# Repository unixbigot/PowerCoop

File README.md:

# PowerCoop

A Power Coop is like a Power Bank but less suckful

## What is a power bank

A power bank is a battery of rechargeable electrical storage cells and some electronics to charge
and discharge.   Almost always USB connectors are used for charging and discharging.

Some have lights or small displays to report the State of Charge (SoC) and possibly the rate of charge/discharge.

They. All.  Suck.   

* Power banks lie egregiously about their capacity
* Power banks ruin cells through sloppy charge/discharge management
* Power banks do not cope with aging cells
* Power banks do not give accurate predictions of available runtime
* Power banks cannot be monitored to tell devices about their capacity and state
* Power banks are unfixable
* Power banks are typically closely coupled to one cell size and/or count

## What is a Power Coop

My vision for a power bank that does not suck

* Fast charging from USB power delivery, and raw DC
* Battery and cell health management (control over charge/discharge levels and rates, cell balancing)
* Multiple independent output channels, each with voltage and current measurement
* Programmable current limiting

Conceptually (per [JPM](https://aus.social/@jpm))  

```text
a battery bank with a bunch of high-power outputs
that all have power displays, also displaying
over Bluetooth, so you can run a phone, a laptop,
a soldering iron, a hotplate, and a couple of
devices under test from it.
```

@voltagex needs a power bank that can wirelessly report its state of charge, in approximately the same size as commercially-available 10,000mAh power banks.

@jpm wants a power bank that you don't need to screw around with, just plug in a USB-C cable and receive power. It needs to be a UPS for a RasPi.

## 6P process

### Problem - what do users want/need

See <https://github.com/unixbigot/PowerCoop/issues>

#### Must Have

* A battery
* USB-C output capable of providing 100W of USB-C PPS power
* USB-C charging at up to 100W
* Display
  * Per-port voltage and current
  * State of charge
  * Remote display via wireless link

#### Should Have

* Support different battery chemistries and number of cells
  * Li-I, LiFePo4, Lead-Acid
* Advanced battery controls
  * Charge limit (eg 80% limit) to prolong service life of Li-I cells
  * Cell balancing
* Advanced output port controls
  * Fixed 5V/3A output for USB-C devices that have broken USB-C CC implementations (eg Raspberry Pi 4)
  * Prevent port turning off on light load
* Modular
  * Battery board - battery charge controller, tells system board how much power is available
  * System board - main display, monitors available power and distributes among ports
  * Port board - receives allowable power level from system, per-port configuration and display
* Only USB-C ports, which reduces design complexity and BOM

#### Nice To Have

* Port board variants with configurable DC input/output or USB-A output
* Any-port charging - I just want to plug the charger in anywhere and it charges
* Able to use power tool battery packs
  * Effectively able to CHARGE power tool battery packs from USB-C!
* Power bank friend on the screen

### Proposal - how are we gonna solve the problem

We gonna make our own power bank that doesn't suck. Hopefully it won't be too much more expensive than power banks that do suck.

### Players - What partial solutions are out there

I (kit, @unixbigot) have or have ordered all of these:

* slightly less sucky power banks
  * <https://aliexpress.com/item/1005004645663172.html>
  * <https://aliexpress.com/item/1005007295821577.html>
  * <https://aliexpress.com/item/1005006988280869.html>
* Off the shelf battery management
  * <https://aliexpress.com/item/1005006071626722.html>
* Microcontroller with PD support
  * <https://aliexpress.com/item/1005005793197807.html>
  * <https://aliexpress.com/item/1005005793197807.html>
* Various DC<->PD modules
  * <https://aliexpress.com/item/1005006463687480.html>
  * <https://aliexpress.com/item/1005006113132068.html>
  * <https://aliexpress.com/item/1005006738365927.html>
  * <https://aliexpress.com/item/1005006572686976.html>

@jpm also has a bunch of similar things, including the CH32X035 dev board and power banks of various suckage.

### Proof of concept - Validate feasibility, select Parts

Splitting the PowerCoop into parts allows us to develop and test different pieces in parallel.  There are 4 main parts to the PowerCoop - the system control, the (main) display, the power ports, and the battery control.

#### System Control

Use the display control SOC? Or should we have a dedicated processor for system (power status and allocation) functions?

#### Main Display

Probably [nRF52840](https://www.nordicsemi.com/Products/nRF52840), maybe other Bluetooth-enabled SOC. TBD what the UI screen/buttons/knobs/etc should be, definitely something that @voltagex would have opinions on.

#### Power Ports

Likely [CH32X035](https://www.wch-ic.com/products/CH32X035.html) as the brains and [TPS55288](https://www.ti.com/product/TPS55288) for the power delivery. TBD if each port should have a separate screen and control.

#### Battery Control

Maybe [LTC4015](https://www.analog.com/en/products/ltc4015.html) as a single unified charge controller, other possibility is to use a cheap SOC (CH32V003?) that abstracts the battery interface so each battery board can have something new and spicy.

### Prototype - Iterate a lot

### Product - deliver on promises

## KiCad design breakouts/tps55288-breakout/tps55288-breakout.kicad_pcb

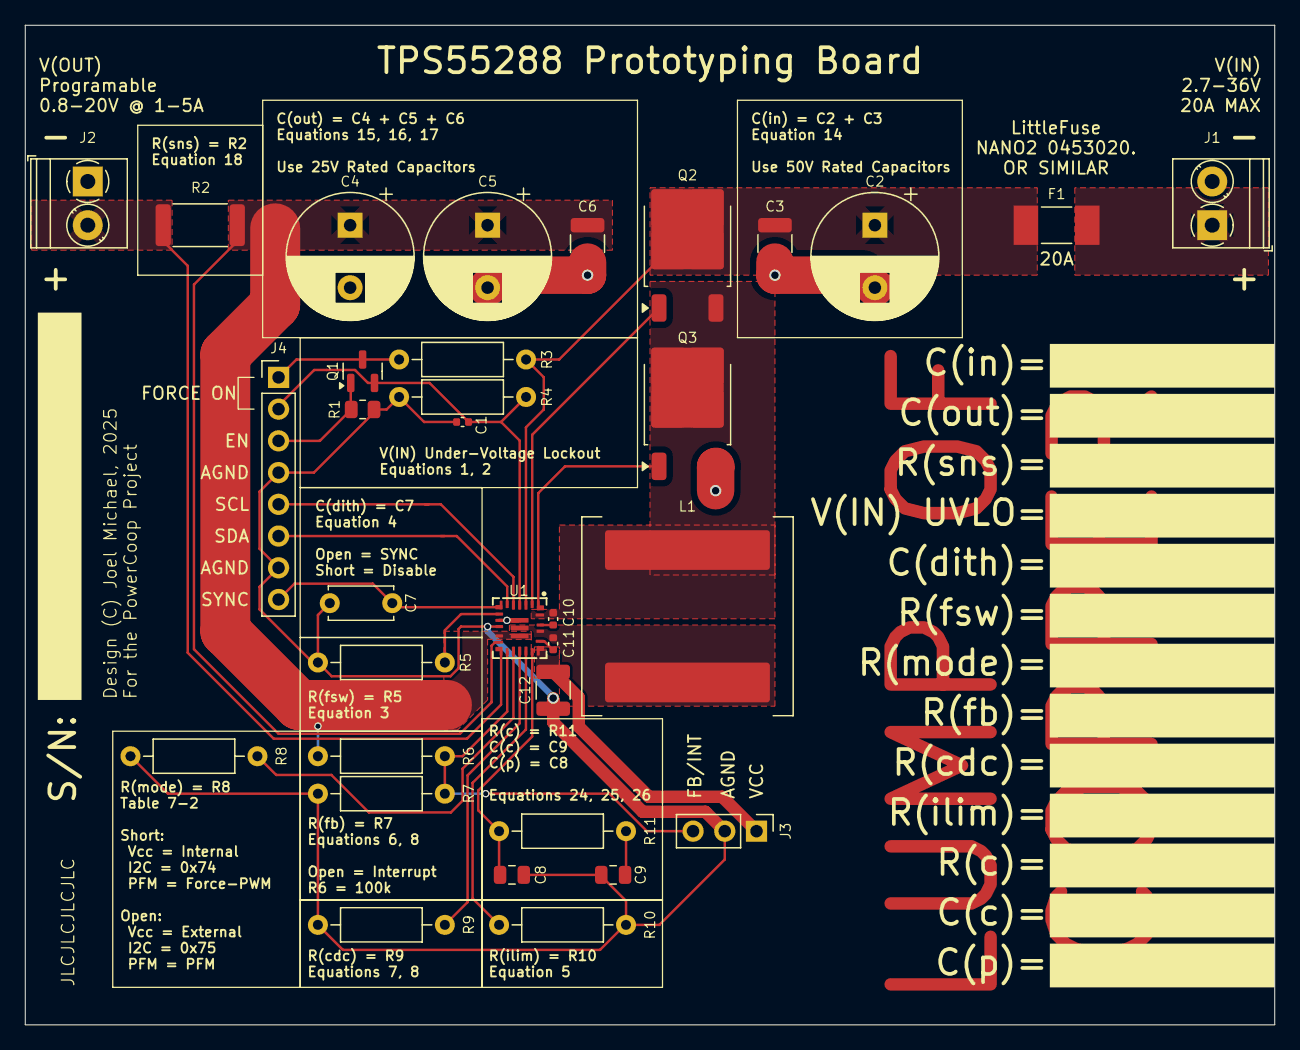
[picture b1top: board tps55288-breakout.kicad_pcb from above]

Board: 2 copper layers, 100.0 x 80.0 mm, 34 parts (1 on the bottom side), 26 nets.

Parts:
C1, C10, C11: 0.1u; C_0402_1005Metric
C2: 100u; CP_Radial_D10.0mm_P5.00mm
C3, C6, C12: 10u; C_1210_3225Metric
C4, C5: 330u; CP_Radial_D10.0mm_P5.00mm
C7: 10n; C_Disc_D5.0mm_W2.5mm_P5.00mm
C8: 150p; C_0805_2012Metric
C9: 15n; C_0805_2012Metric
F1: 20A; Fuse_Littelfuse-NANO2-451_453
J1, J2: Screw_Terminal_01x02; TerminalBlock_Phoenix_PT-1,5-2-3.5-H_1x02_P3.50mm_Horizontal
J3: Conn_01x10_Pin; PinHeader_1x03_P2.54mm_Vertical
J4: Conn_01x06_Pin; PinHeader_1x08_P2.54mm_Vertical
JP1: SolderJumper_2_Bridged; SolderJumper-2_P1.3mm_Bridged2Bar_Pad1.0x1.5mm
L1: 4.7u; L_Coilcraft_XAL1510-682
Q1: 2N7002K; SOT-23
Q2, Q3: QM6006D; TO-252-2
R1: 10k; R_0805_2012Metric
R2: 10m; R_2512_6332Metric
R3: 4.3k; R_Axial_DIN0207_L6.3mm_D2.5mm_P10.16mm_Horizontal
R4, R7: 1k; R_Axial_DIN0207_L6.3mm_D2.5mm_P10.16mm_Horizontal
R5: 47k; R_Axial_DIN0207_L6.3mm_D2.5mm_P10.16mm_Horizontal
R6: 100k; R_Axial_DIN0207_L6.3mm_D2.5mm_P10.16mm_Horizontal
R8: 0; R_Axial_DIN0207_L6.3mm_D2.5mm_P10.16mm_Horizontal
R9: 20k; R_Axial_DIN0207_L6.3mm_D2.5mm_P10.16mm_Horizontal
R10: 16k; R_Axial_DIN0207_L6.3mm_D2.5mm_P10.16mm_Horizontal
R11: 91k; R_Axial_DIN0207_L6.3mm_D2.5mm_P10.16mm_Horizontal
U1: TPS55288RPMR; VQFN-HR-26_L4.0-W3.5_TPS55288RPMR

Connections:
/AGND: C1.1, C7.1, C8.1, C9.1, C12.1, J3.2, J4.4, J4.7, JP1.2 (B), R1.1, R4.2, R5.2, R7.2, R8.2, R9.2, R10.2, U1.10 (AGND)
/BOOT1: C10.1, U1.22 (BOOT1)
/BOOT2: C11.1, U1.20 (BOOT2)
/CDC: R9.1, U1.16 (CDC)
/COMP: C8.2, R11.1, U1.18 (COMP)
/DITH/SYNC: C7.2, J4.8, U1.7 (DITH/SYNC)
/DR1H: Q2.1 (G), U1.2 (DR1H)
/DR1L: Q3.1 (G), U1.1 (DR1L)
/EN: J4.3, Q1.1 (G), R1.2
/EN/UVLO: C1.2, J4.2, Q1.2 (S), R4.1, U1.4 (EN/UVLO)
/FB/INT: J3.3, R6.2, R7.1, U1.14 (FB/INT)
/FSW: R5.1, U1.8 (FSW)
/ILIM: R10.1, U1.17 (ILIM)
/ISN: J2.2, R2.1, U1.13 (ISN)
/MODE: R8.1, U1.15 (MODE)
/ON: J4.1, Q1.3 (D), R3.2
/SCL: J4.5, U1.5 (SCL)
/SDA: J4.6, U1.6 (SDA)
/SW1: C10.2, L1.1, Q2.3 (S), Q3.2 (D), U1.23 (SW1)
/SW2: C11.2, L1.2, U1.21 (SW2), U1.25 (SW2)
/VCC: C12.2, J3.1, U1.19 (VCC)
/VIN: C2.1, C3.2, F1.1, Q2.2 (D), R3.1, U1.3 (VIN)
/VOUT: C4.1, C5.1, C6.2, R2.2, R6.1, U1.11 (VOUT), U1.12 (ISP), U1.26 (VOUT)
GND: C2.2, C3.1, C4.2, C5.2, C6.1, J1.2, J2.1, JP1.1 (A), Q3.3 (S), U1.9 (PGND), U1.24 (PGND)
unnamed: C9.2, R11.2
unnamed: F1.2, J1.1

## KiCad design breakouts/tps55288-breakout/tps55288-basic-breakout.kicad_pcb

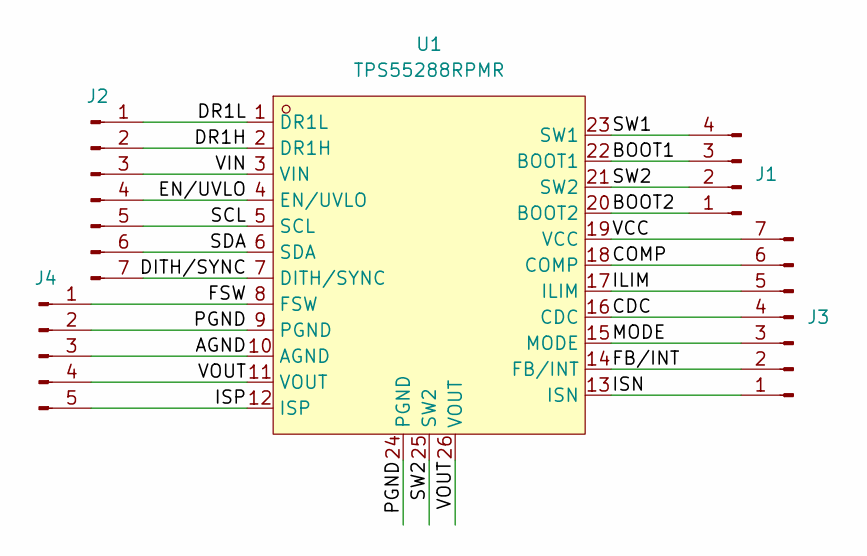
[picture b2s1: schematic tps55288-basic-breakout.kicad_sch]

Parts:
J1: Conn_01x04_Pin; PinHeader_1x04_P2.54mm_Vertical
J2, J3: Conn_01x07_Pin; PinHeader_1x07_P2.54mm_Vertical
J4: Conn_01x05_Pin; PinHeader_1x05_P2.54mm_Vertical
U1: TPS55288RPMR; VQFN-HR-26_L4.0-W3.5_TPS55288RPMR; LCSC Part C2864583

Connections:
/AGND: J4.3, U1.10 (AGND)
/BOOT1: J1.3, U1.22 (BOOT1)
/BOOT2: J1.1, U1.20 (BOOT2)
/CDC: J3.4, U1.16 (CDC)
/COMP: J3.6, U1.18 (COMP)
/DITH/SYNC: J2.7, U1.7 (DITH/SYNC)
/DR1H: J2.2, U1.2 (DR1H)
/DR1L: J2.1, U1.1 (DR1L)
/EN/UVLO: J2.4, U1.4 (EN/UVLO)
/FB/INT: J3.2, U1.14 (FB/INT)
/FSW: J4.1, U1.8 (FSW)
/ILIM: J3.5, U1.17 (ILIM)
/ISN: J3.1, U1.13 (ISN)
/ISP: J4.5, U1.12 (ISP)
/MODE: J3.3, U1.15 (MODE)
/PGND: J4.2, U1.9 (PGND), U1.24 (PGND)
/SCL: J2.5, U1.5 (SCL)
/SDA: J2.6, U1.6 (SDA)
/SW1: J1.4, U1.23 (SW1)
/SW2: J1.2, U1.21 (SW2), U1.25 (SW2)
/VCC: J3.7, U1.19 (VCC)
/VIN: J2.3, U1.3 (VIN)
/VOUT: J4.4, U1.11 (VOUT), U1.26 (VOUT)

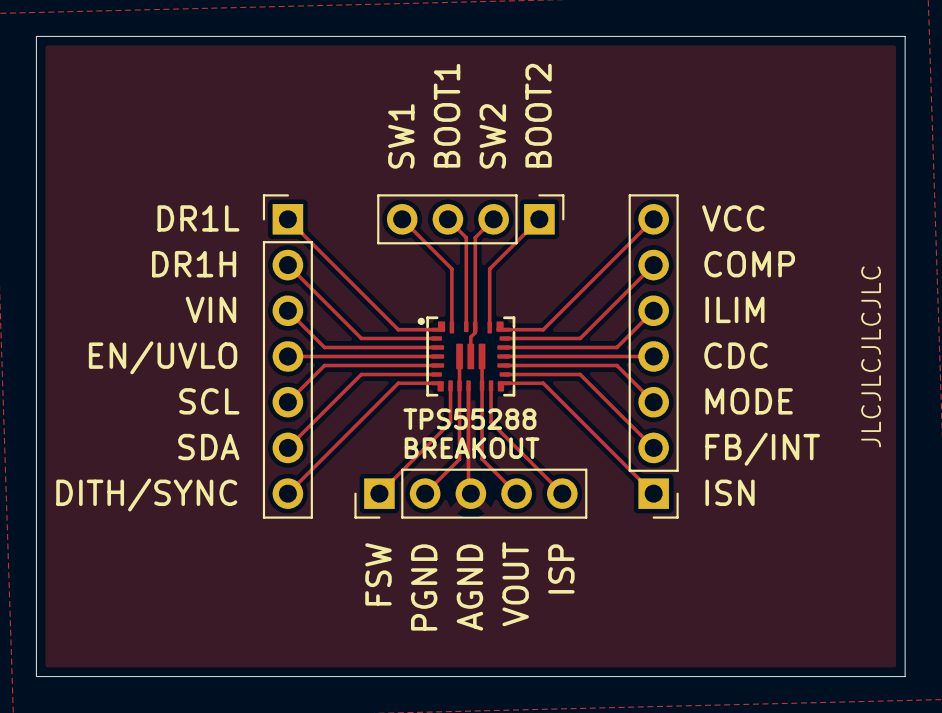
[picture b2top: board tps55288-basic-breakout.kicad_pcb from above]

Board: 2 copper layers, 48.3 x 35.6 mm, 5 parts (0 on the bottom side), 23 nets.

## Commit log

2025-01-31 Braindump some products that are pieces of the puzzle
2025-02-03 expand 6P process section with details from issues; minor markdown correctness fixes
2025-02-05 Add component libraries and skeleton of breakout pcbs
2025-02-11 git gooder
2025-02-11 use parameters and relative paths to reference footprints and symbols for this project
2025-02-26 initial TPS55288 design notes
2025-02-26 TPS55288 design inductor result tables
2025-02-27 TPS55288 design capacitor result tables
2025-03-08 finish schematic equations... by using the calculator that TI provides
2025-03-18 re-create footprint model from datasheet, because the LCSC one is very wrong...
2025-03-18 ultra-basic breakout to test footprint
2025-03-18 first pass at full-featured TPS55288 breakout board
2025-03-28 prototype board updates - add many silkscreen things
2025-03-28 new breakout: TPS55288 plus WeAct CH32X035CoreBoard
